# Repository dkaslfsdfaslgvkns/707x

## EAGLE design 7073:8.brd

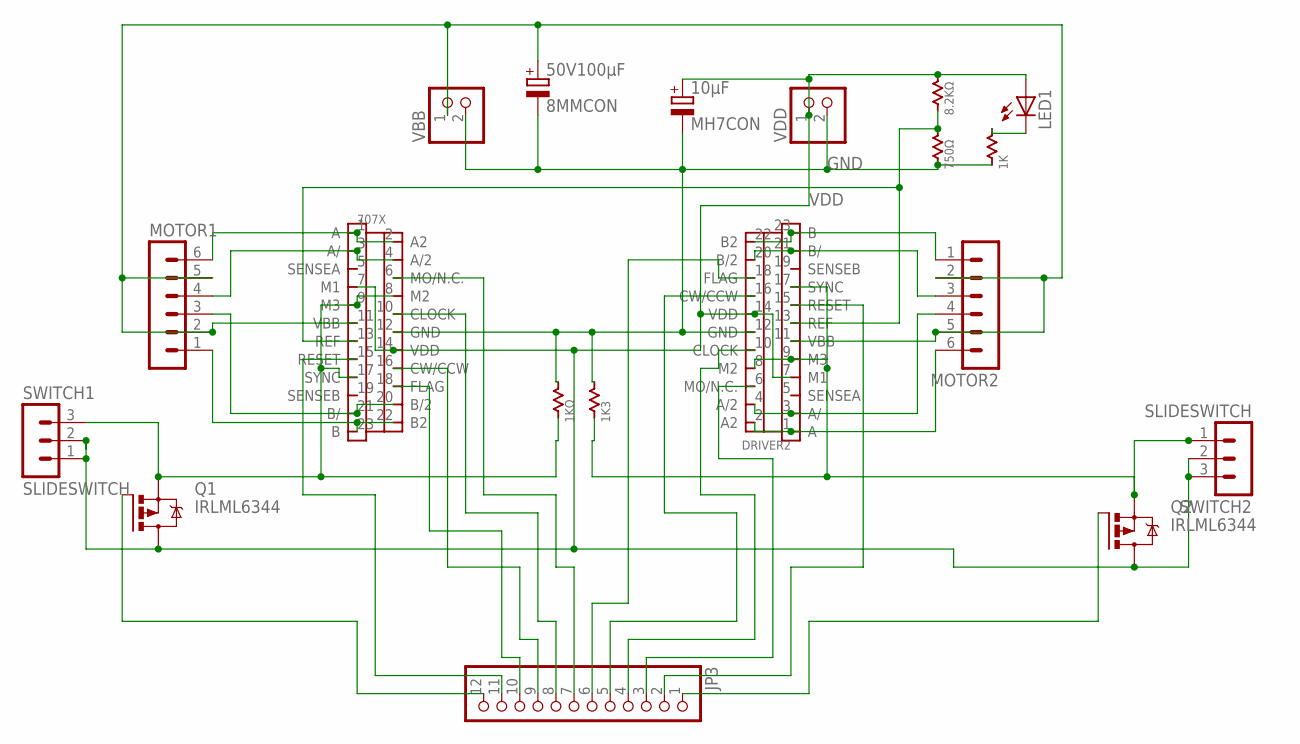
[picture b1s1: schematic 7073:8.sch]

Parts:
1K, 1K3, 1KΩ: R1608; C1608
8.2KΩ, 750Ω: 1/6W; 1/6WRESISTANCE
10μF: MH7CON
50V100μF: 8MMCON; 50V100FCON
707X: SLA707X; 23-2PINHEAD
DRIVER2: SLA707X; 23-2PINHEAD
JP3: PINHD-1X12; 1X12
LED1: OPTOCHIPLEDLED; CHIP
MOTOR1, MOTOR2: MA06-1
Q1, Q2: IRLML6344; MICRO3
SWITCH1, SWITCH2: SLIDESWITCH; M251
VBB: PINHD-1X2; 1X02
VDD: PINHD-1X2; 1X02

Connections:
GND: 1K.2 (A), 1K3.1 (B), 1KΩ.1 (B), 10μF.P$2 (-), 50V100μF.P$2 (-), 707X.12 (GND), 750Ω.P$2 (A), DRIVER2.12 (GND), VBB.2, VDD.2
unnamed: 707X.22 (B2), 707X.23 (B), MOTOR1.1
unnamed: 707X.20 (B/2), 707X.21 (B/), MOTOR1.3
unnamed: 707X.1 (A), 707X.2 (A2), MOTOR1.6
unnamed: 707X.3 (A/), 707X.4 (A/2), MOTOR1.4
unnamed: DRIVER2.1 (A), DRIVER2.2 (A2), MOTOR2.6
unnamed: DRIVER2.3 (A/), DRIVER2.4 (A/2), MOTOR2.4
unnamed: DRIVER2.20 (B/2), DRIVER2.21 (B/), MOTOR2.3
unnamed: DRIVER2.22 (B2), DRIVER2.23 (B), MOTOR2.1
unnamed: 1K.1 (B), LED1.P$2 (C)
unnamed: 707X.15 (RESET), JP3.11
unnamed: JP3.12, Q1.1 (G)
unnamed: 50V100μF.P$1 (+), 707X.11 (VBB), DRIVER2.11 (VBB), MOTOR1.2, MOTOR1.5, MOTOR2.2, MOTOR2.5, VBB.1
unnamed: 707X.18 (FLAG), JP3.10
unnamed: 8.2KΩ.P$2 (A), 707X.13 (REF), 750Ω.P$1 (B), DRIVER2.13 (REF)
unnamed: 1K3.2 (A), DRIVER2.8 (M2), DRIVER2.9 (M3), DRIVER2.17 (SYNC), Q2.2 (S), SWITCH2.1
unnamed: 1KΩ.2 (A), 707X.8 (M2), 707X.9 (M3), 707X.17 (SYNC), Q1.2 (S), SWITCH1.3
unnamed: 707X.16 (CW/CCW), JP3.9
unnamed: 707X.10 (CLOCK), JP3.8
unnamed: 707X.6 (MO/N.C.), JP3.7
unnamed: JP3.1, Q2.1 (G)
unnamed: DRIVER2.15 (RESET), JP3.2
unnamed: DRIVER2.6 (MO/N.C.), JP3.3
unnamed: DRIVER2.10 (CLOCK), JP3.4
unnamed: DRIVER2.16 (CW/CCW), JP3.5
unnamed: DRIVER2.18 (FLAG), JP3.6
VDD: 8.2KΩ.P$1 (B), 10μF.P$1 (+), 707X.7 (M1), 707X.14 (VDD), DRIVER2.7 (M1), DRIVER2.14 (VDD), LED1.P$1 (A), Q1.3 (D), Q2.3 (D), SWITCH1.1, SWITCH1.2, SWITCH2.2, SWITCH2.3, VDD.1

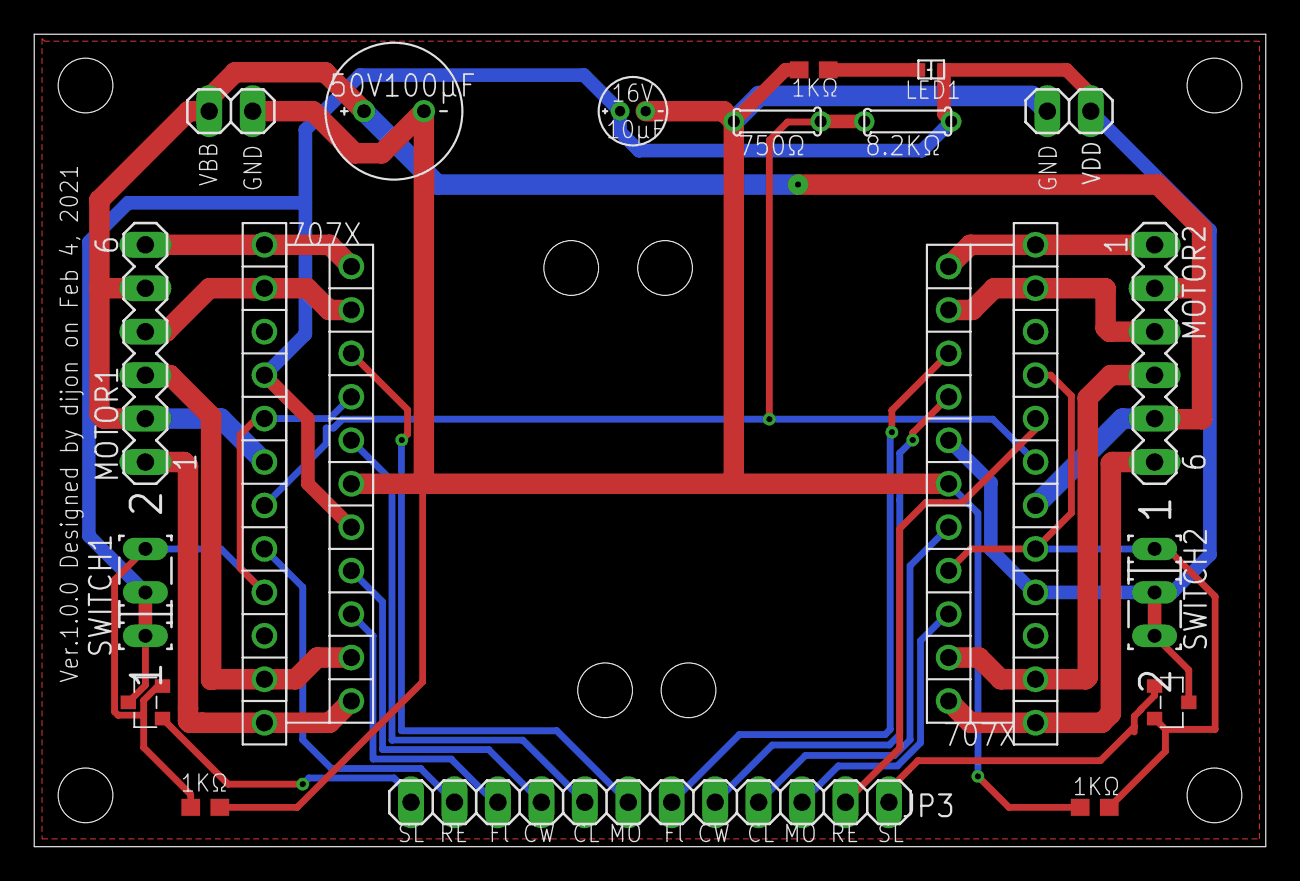
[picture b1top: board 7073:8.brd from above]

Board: 2 copper layers, 72.0 x 47.5 mm, 19 parts (0 on the bottom side), 27 nets.

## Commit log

2021-02-15 LICENSE
2021-02-15 Update LICENSE
